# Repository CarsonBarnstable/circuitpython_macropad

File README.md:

# circuitpython_macropad
### Details for a Hand-Built Macropad (and its Background Code)
##### *All plans and files originally from University of Alberta's ELKO Engineering Garage*
##### *Controller Software was Partially Developed by Myself, all other Code is Not my own work.*

# Overview
Deatils (Ideas)

# Building the Macropad
Deatils (steps)

### Files
Deatils (links)

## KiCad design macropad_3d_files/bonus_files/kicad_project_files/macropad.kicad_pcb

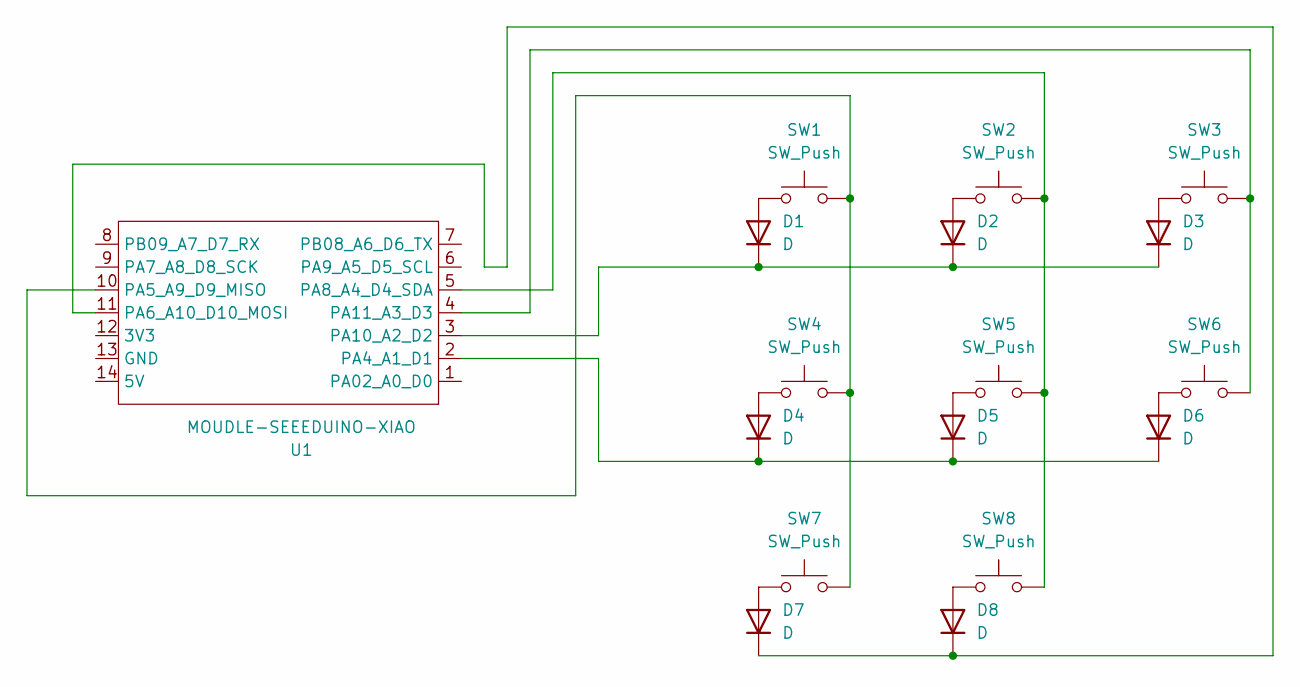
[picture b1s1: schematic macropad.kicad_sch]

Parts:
D1, D2, D3, D4, D5, D6, D7, D8: D; D_SOD-123
SW1, SW2, SW3, SW4, SW5, SW6, SW7, SW8: SW_Push; SW_Cherry_MX_1.00u_PCB
U1: MOUDLE-SEEEDUINO-XIAO; MOUDLE14P-2.54-21X17.8MM

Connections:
unnamed: D1.1 (K), D2.1 (K), D3.1 (K), U1.3 (PA10_A2_D2)
unnamed: D1.2 (A), SW1.1
unnamed: D2.2 (A), SW2.1
unnamed: D3.2 (A), SW3.1
unnamed: D4.1 (K), D5.1 (K), D6.1 (K), U1.2 (PA4_A1_D1)
unnamed: D4.2 (A), SW4.1
unnamed: D5.2 (A), SW5.1
unnamed: D6.2 (A), SW6.1
unnamed: D7.1 (K), D8.1 (K), U1.11 (PA6_A10_D10_MOSI)
unnamed: D7.2 (A), SW7.1
unnamed: D8.2 (A), SW8.1
unnamed: SW1.2, SW4.2, SW7.2, U1.10 (PA5_A9_D9_MISO)
unnamed: SW2.2, SW5.2, SW8.2, U1.5 (PA8_A4_D4_SDA)
unnamed: SW3.2, SW6.2, U1.4 (PA11_A3_D3)

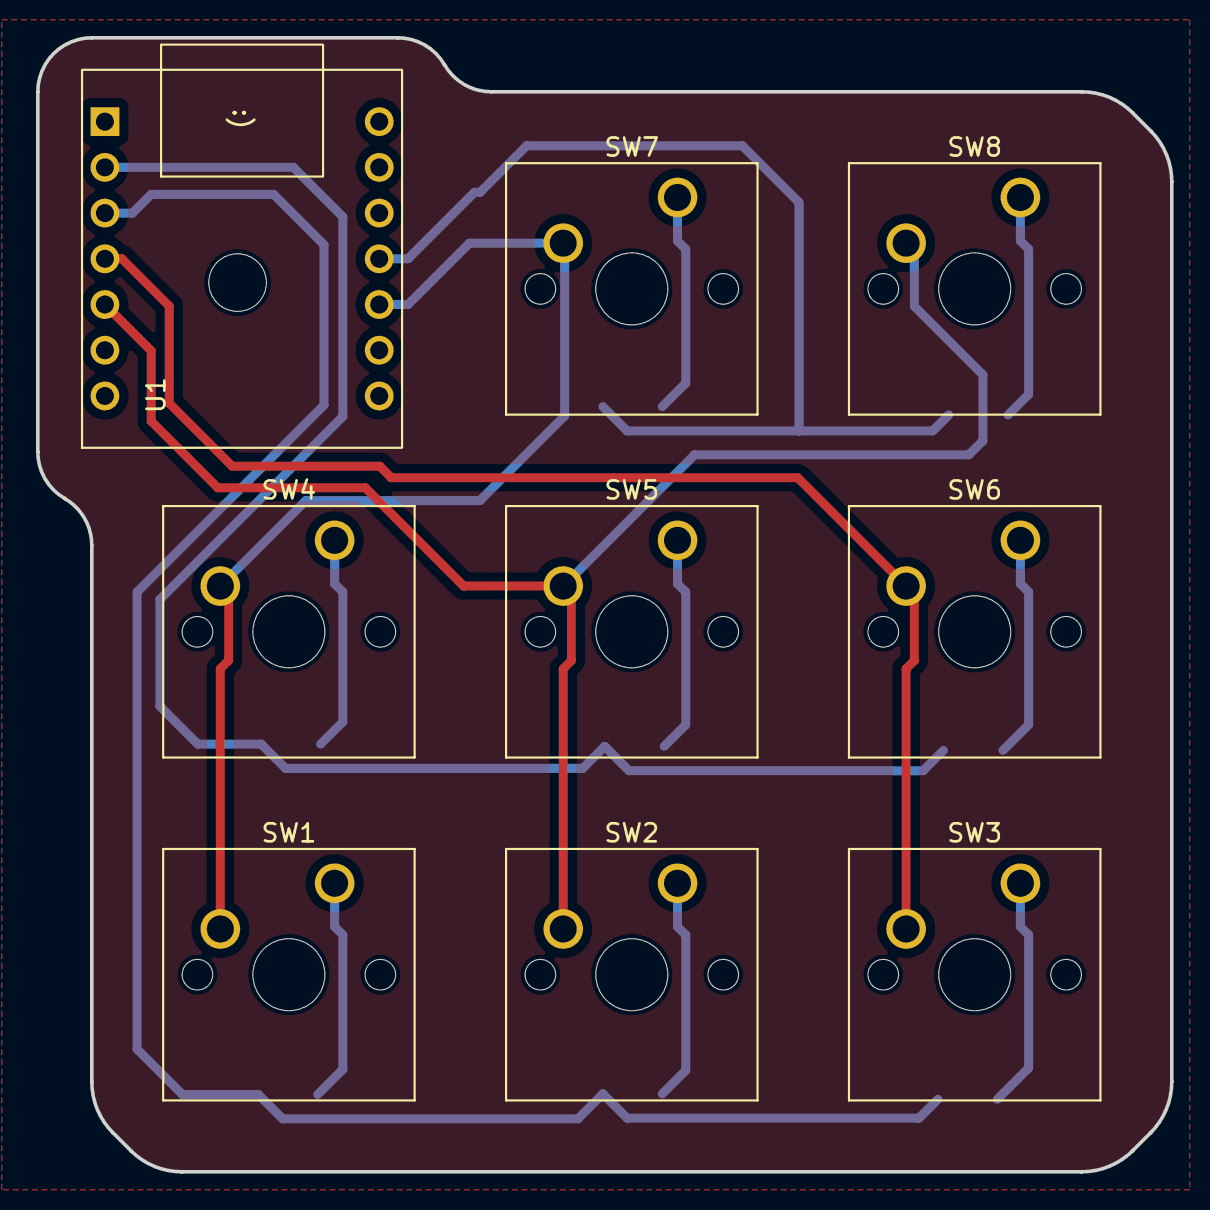
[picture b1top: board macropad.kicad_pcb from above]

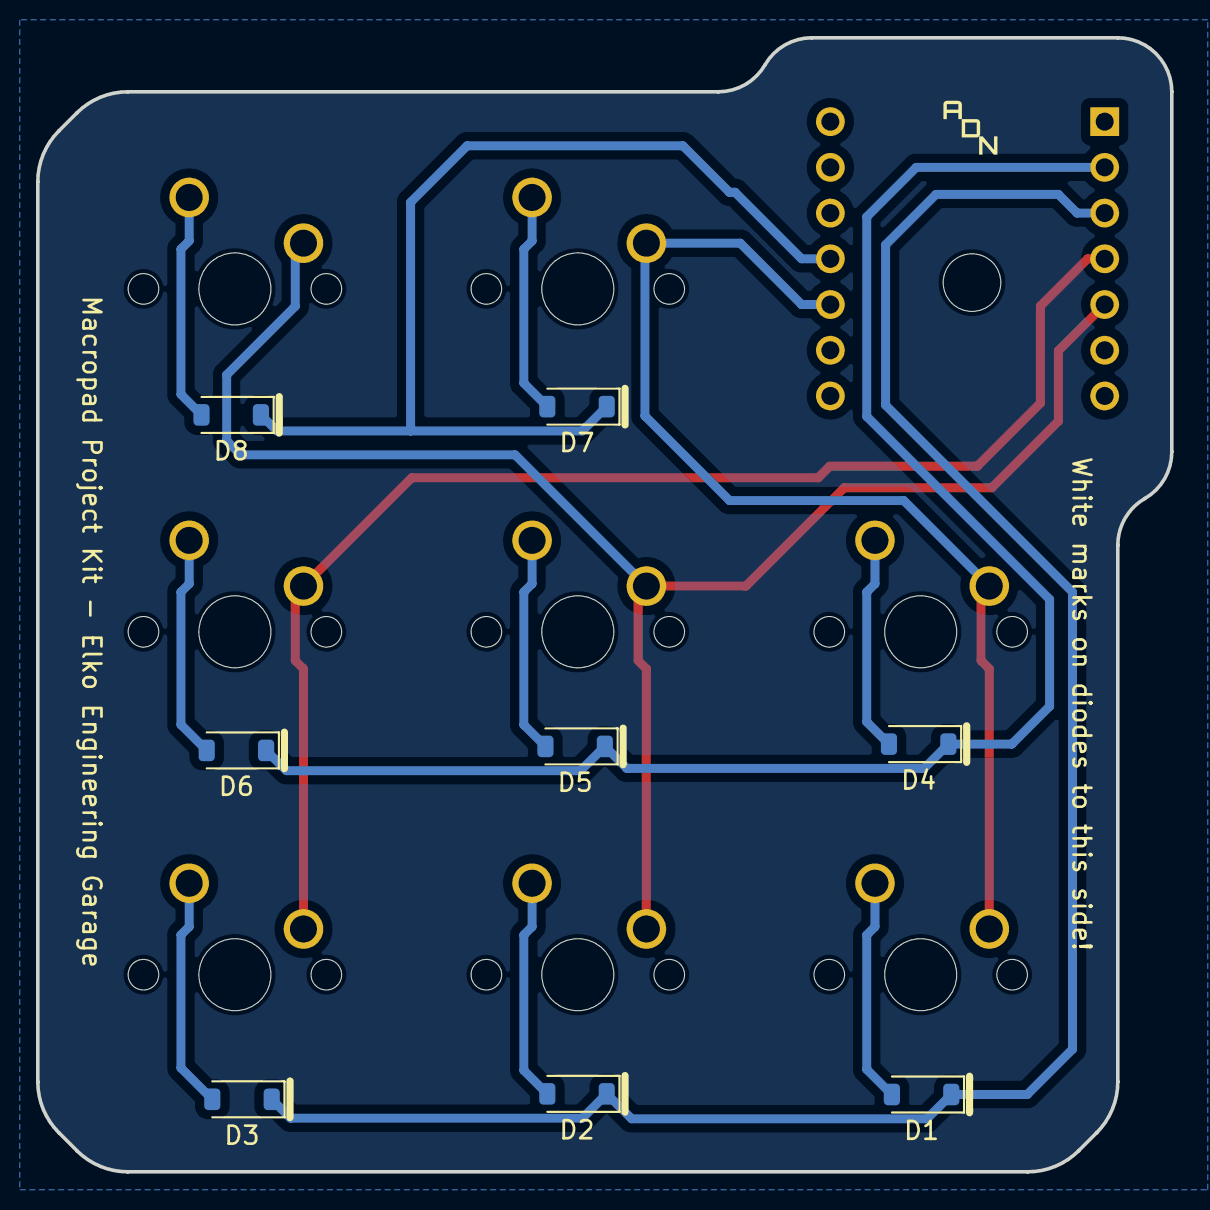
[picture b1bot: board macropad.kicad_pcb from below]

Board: 2 copper layers, 63.0 x 63.0 mm, 18 parts (8 on the bottom side), 14 nets.

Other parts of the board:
 : MountingHole_3.2mm_M3

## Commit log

2023-12-11 Create main code.py file
2023-12-11 Adding firmware files via backup
2023-12-11 Adding standard circuitpython library via upload
2023-12-11 Adding no_log file
2023-12-11 Updated initial README
2023-12-20 Renamed 'firmware' folder to 'controller_software'
2023-12-20 Adding Files Needed for Reconstruction
2023-12-20 Updated README.md for Clarity
2024-01-16 Created Photos README
2024-01-16 Adding Photos via Upload
2024-01-16 Adding Photos to Photos README
2024-01-16 Adding End Result Photo to Main README
